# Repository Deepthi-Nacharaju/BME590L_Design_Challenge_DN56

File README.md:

# BME590_Design_Challenge_DN56
# This Design Skills Challenge will test our knowledge of mechanical, electrical, and software design.

# Functional Specs are as follows

# LED light that is button-activated to switch between the following operating modes:
# Off
# Brightest
# Intermediate Brightness
# Least Bright
# Flashing @ 2 Hz
# Self-contained device with LED and button exposed.
# Extra credit possibilities:
# Battery life indicator
# Waterproof enclosure

# Constraints are as follows

# Run on single battery up to 9 V
# Electronics connected to a single PCB (can be single- or double-sided)
# Cannot weight more than 1 lb
# Cannot have a single dimension > 6 in
# Cannot cost more than $50 to duplicate unit
# Battery must be easily replaceable

# Projects will be evaluated according to the following criteria
# Minimize weight

# Minimize size

# Maximize Brightest mode

# Minimize power draw / maximize battery life

# Survive 3 foot drop with battery installed

# Create-and-maintain a GitHub project repository to maintain version history of:

# Mechanical CAD (PDFs + more)
# Electronic CAD (PDFs + more)
# Software
# Testing data
# Design history / notes
# Specification sheets
# Usage notes (README.md)
# Kanban board / Issues / Milestones

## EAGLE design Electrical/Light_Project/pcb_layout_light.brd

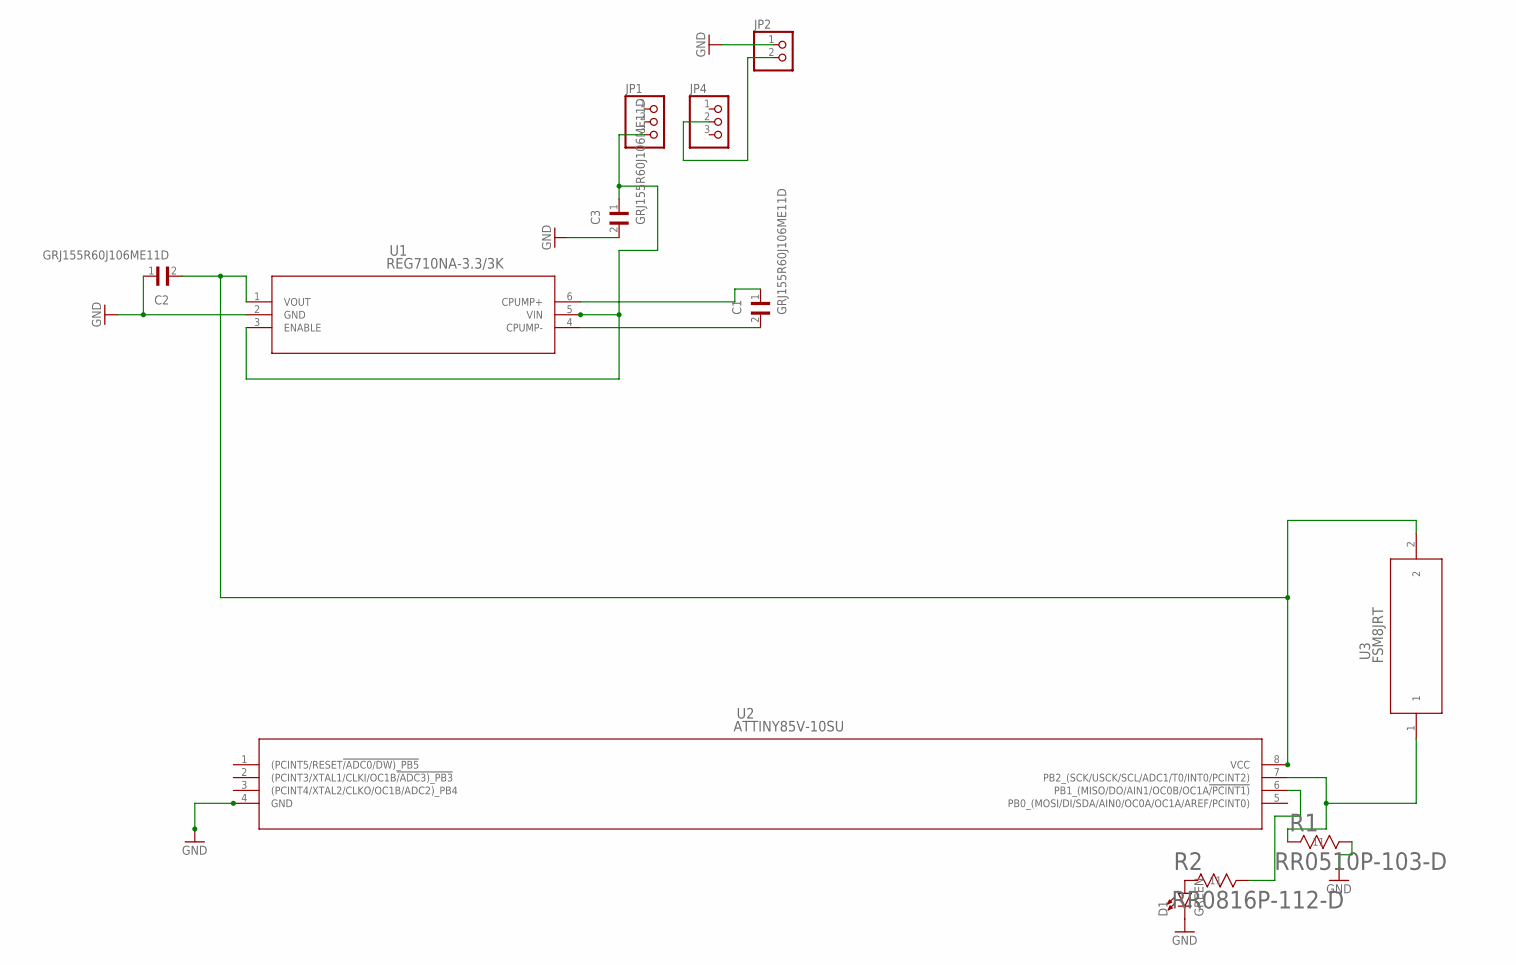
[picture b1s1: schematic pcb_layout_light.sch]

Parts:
C1, C2, C3: GRJ155R60J106ME11D; CAPC1005X55N
D1: GREEN; LED-0603
JP1, JP4: PINHD-1X3; 1X03
JP2: PINHD-1X2; 1X02
R1: RR0510P-103-D; RES_0510
R2: RR0816P-112-D; RES_0816
U1: REG710NA-3.3/3K; DBV6
U2: ATTINY85V-10SU; 8S2
U3: FSM8JRT; SWITCH_FSM4JRT

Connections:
GND: C2.1, C3.2, D1.C, JP2.1, R1.2 (22), U1.2 (GND), U2.4 (GND)
unnamed: C2.2, U1.1 (VOUT), U2.8 (VCC), U3.2
unnamed: C1.1, U1.6 (CPUMP+)
unnamed: C1.2, U1.4 (CPUMP-)
unnamed: R1.1 (11), U2.7 (PB2_(SCK/USCK/SCL/ADC1/T0/INT0/PCINT2)), U3.1
unnamed: D1.A, R2.1 (11)
unnamed: R2.2 (22), U2.6 (PB1_(MISO/DO/AIN1/OC0B/OC1A!/PCINT1))
unnamed: C3.1, JP1.3, U1.3 (ENABLE), U1.5 (VIN)
unnamed: JP2.2, JP4.2

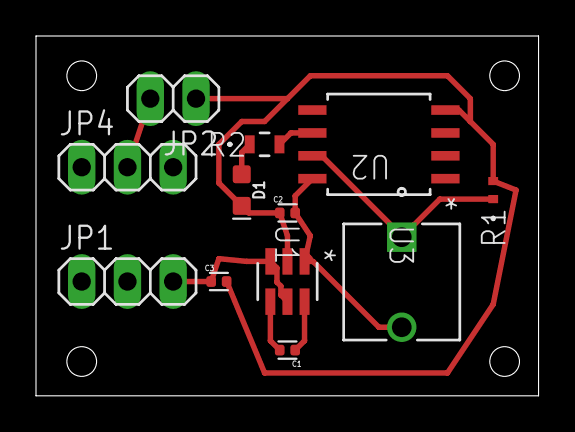
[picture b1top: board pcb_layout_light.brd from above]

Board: 2 copper layers, 27.9 x 20.0 mm, 12 parts (0 on the bottom side), 9 nets.

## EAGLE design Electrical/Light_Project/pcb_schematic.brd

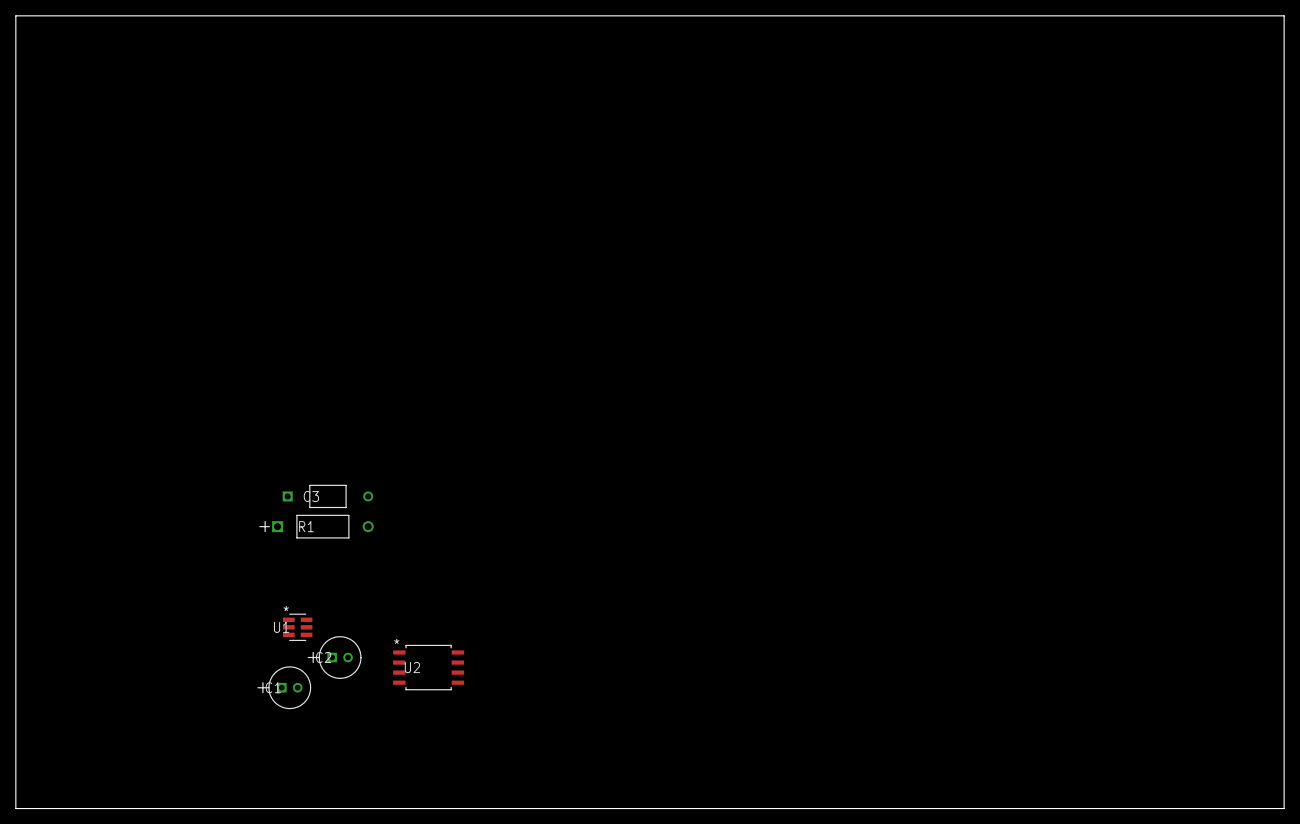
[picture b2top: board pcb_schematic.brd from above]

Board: 2 copper layers, 160.0 x 100.0 mm, 6 parts (0 on the bottom side), 6 nets, no tracks yet.

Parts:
C1, C2: UPS1H2R2MDD1TD; U1-E
C3: C410C224M5U5TA7200; CAP_C410
R1: CF14JT10K0; STA_CF14
U1: REG710NA-3.3/3K; DBV6
U2: ATTINY85V-10SU; 8S2

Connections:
GND: C1.2, R1.1, U1.2, U2.4
unnamed: C1.1, U1.1, U2.8
unnamed: C3.1, U1.6
unnamed: C3.2, U1.4
unnamed: C2.1, U1.5
unnamed: R1.2, U2.5

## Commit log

2018-09-20 Create new folders
2018-09-20 Create more new folders
2018-10-01 Add Block Diagram
2018-10-01 Create Block Diagram Image
2018-10-28 Add EAGLE files and Block Diagram
2018-10-29 add pcb
2018-10-30 didnt add files
2018-10-30 add arduino code
2018-10-30 add all files that have changed
2018-11-01 milestone 3
2018-11-07 Route PCB (not optimized)
2018-11-08 use surface mount resistor in diagram
2018-11-08 add pdf of new layout
2018-11-08 add holes on pcb
2018-11-13 update PCB layout with LED
2018-11-19 add solidworks files for milestone 5
2018-11-20 add updated solidwords files with screws and nuts
2018-11-20 change route width
2018-11-27 Update bypass cap to go to ground and add header pins for switch and power supply
2018-12-08 Add BOM
2018-12-10 Final solidworks files

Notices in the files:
parts and their libraries:
SparkFun-LED: Licensing: Creative Commons ShareAlike 4.0 International - https://creativecommons.org/licenses/by-sa/4.0
